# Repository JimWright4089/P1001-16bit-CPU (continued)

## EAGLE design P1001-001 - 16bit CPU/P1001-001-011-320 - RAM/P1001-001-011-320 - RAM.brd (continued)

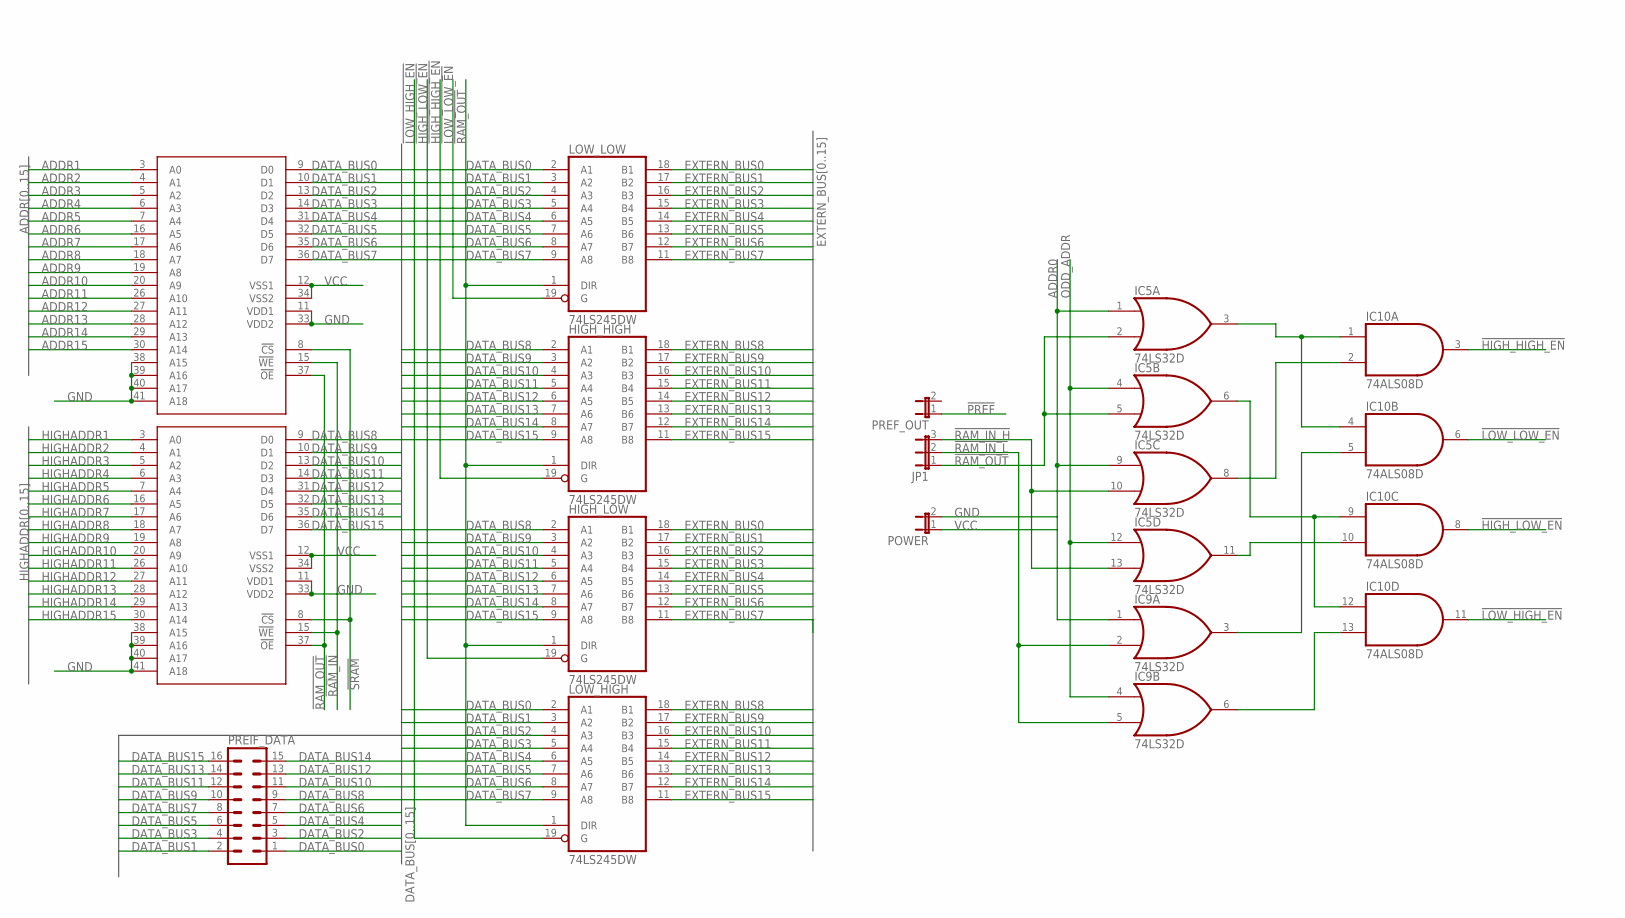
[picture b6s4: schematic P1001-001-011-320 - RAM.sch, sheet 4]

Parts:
HIGH_HIGH: 74LS245DW; SO20W
HIGH_LOW: 74LS245DW; SO20W
IC5, IC9: 74LS32D; SO14
IC10: 74ALS08D; SO14
JP1: JP2E; JP2
LOW_HIGH: 74LS245DW; SO20W
LOW_LOW: 74LS245DW; SO20W
MEM_HIGH: IDT71V424S; TSOP44-II
MEM_LOW: IDT71V424S; TSOP44-II
POWER: JP1E; JP1
PREF_OUT: JP1E; JP1
PREIF_DATA: ML16

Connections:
!HIGH_HIGH_EN: HIGH_HIGH.19 (G), IC10.3 (O)
!HIGH_LOW_EN: HIGH_LOW.19 (G), IC10.8 (O)
!LOW_HIGH_EN: IC10.11 (O), LOW_HIGH.19 (G)
!LOW_LOW_EN: IC10.6 (O), LOW_LOW.19 (G)
!PREF: PREF_OUT.1; also elsewhere on the board
!RAM_IN: MEM_HIGH.15 (!WE), MEM_LOW.15 (!WE)
!RAM_IN_H: IC5.10 (I1), IC5.13 (I1), JP1.3
!RAM_IN_L: IC9.2 (I1), IC9.5 (I1), JP1.2
!RAM_OUT: HIGH_HIGH.1 (DIR), HIGH_LOW.1 (DIR), IC5.2 (I1), IC5.5 (I1), JP1.1, LOW_HIGH.1 (DIR), LOW_LOW.1 (DIR), MEM_HIGH.37 (!OE), MEM_LOW.37 (!OE)
!SRAM: MEM_HIGH.8 (!CS), MEM_LOW.8 (!CS); also elsewhere on the board
ADDR0: IC5.1 (I0), IC5.9 (I0), IC9.1 (I0); also elsewhere on the board
ADDR1: MEM_LOW.3 (A0); also elsewhere on the board
ADDR2: MEM_LOW.4 (A1); also elsewhere on the board
ADDR3: MEM_LOW.5 (A2); also elsewhere on the board
ADDR4: MEM_LOW.6 (A3); also elsewhere on the board
ADDR5: MEM_LOW.7 (A4); also elsewhere on the board
ADDR6: MEM_LOW.16 (A5); also elsewhere on the board
ADDR7: MEM_LOW.17 (A6); also elsewhere on the board
ADDR8: MEM_LOW.18 (A7); also elsewhere on the board
ADDR9: MEM_LOW.19 (A8); also elsewhere on the board
ADDR10: MEM_LOW.20 (A9); also elsewhere on the board
ADDR11: MEM_LOW.26 (A10); also elsewhere on the board
ADDR12: MEM_LOW.27 (A11); also elsewhere on the board
ADDR13: MEM_LOW.28 (A12); also elsewhere on the board
ADDR14: MEM_LOW.29 (A13); also elsewhere on the board
ADDR15: MEM_LOW.30 (A14); also elsewhere on the board
DATA_BUS0: LOW_HIGH.2 (A1), LOW_LOW.2 (A1), MEM_LOW.9 (D0), PREIF_DATA.1; also elsewhere on the board
DATA_BUS1: LOW_HIGH.3 (A2), LOW_LOW.3 (A2), MEM_LOW.10 (D1), PREIF_DATA.2; also elsewhere on the board
DATA_BUS2: LOW_HIGH.4 (A3), LOW_LOW.4 (A3), MEM_LOW.13 (D2), PREIF_DATA.3; also elsewhere on the board
DATA_BUS3: LOW_HIGH.5 (A4), LOW_LOW.5 (A4), MEM_LOW.14 (D3), PREIF_DATA.4; also elsewhere on the board
DATA_BUS4: LOW_HIGH.6 (A5), LOW_LOW.6 (A5), MEM_LOW.31 (D4), PREIF_DATA.5; also elsewhere on the board
DATA_BUS5: LOW_HIGH.7 (A6), LOW_LOW.7 (A6), MEM_LOW.32 (D5), PREIF_DATA.6; also elsewhere on the board
DATA_BUS6: LOW_HIGH.8 (A7), LOW_LOW.8 (A7), MEM_LOW.35 (D6), PREIF_DATA.7; also elsewhere on the board
DATA_BUS7: LOW_HIGH.9 (A8), LOW_LOW.9 (A8), MEM_LOW.36 (D7), PREIF_DATA.8; also elsewhere on the board
DATA_BUS8: HIGH_HIGH.2 (A1), HIGH_LOW.2 (A1), MEM_HIGH.9 (D0), PREIF_DATA.9; also elsewhere on the board
DATA_BUS9: HIGH_HIGH.3 (A2), HIGH_LOW.3 (A2), MEM_HIGH.10 (D1), PREIF_DATA.10; also elsewhere on the board
DATA_BUS10: HIGH_HIGH.4 (A3), HIGH_LOW.4 (A3), MEM_HIGH.13 (D2), PREIF_DATA.11; also elsewhere on the board
DATA_BUS11: HIGH_HIGH.5 (A4), HIGH_LOW.5 (A4), MEM_HIGH.14 (D3), PREIF_DATA.12; also elsewhere on the board
DATA_BUS12: HIGH_HIGH.6 (A5), HIGH_LOW.6 (A5), MEM_HIGH.31 (D4), PREIF_DATA.13; also elsewhere on the board
DATA_BUS13: HIGH_HIGH.7 (A6), HIGH_LOW.7 (A6), MEM_HIGH.32 (D5), PREIF_DATA.14; also elsewhere on the board
DATA_BUS14: HIGH_HIGH.8 (A7), HIGH_LOW.8 (A7), MEM_HIGH.35 (D6), PREIF_DATA.15; also elsewhere on the board
DATA_BUS15: HIGH_HIGH.9 (A8), HIGH_LOW.9 (A8), MEM_HIGH.36 (D7), PREIF_DATA.16; also elsewhere on the board
EXTERN_BUS0: HIGH_LOW.18 (B1), LOW_LOW.18 (B1); also elsewhere on the board
EXTERN_BUS1: HIGH_LOW.17 (B2), LOW_LOW.17 (B2); also elsewhere on the board
EXTERN_BUS2: HIGH_LOW.16 (B3), LOW_LOW.16 (B3); also elsewhere on the board
EXTERN_BUS3: HIGH_LOW.15 (B4), LOW_LOW.15 (B4); also elsewhere on the board
EXTERN_BUS4: HIGH_LOW.14 (B5), LOW_LOW.14 (B5); also elsewhere on the board
EXTERN_BUS5: HIGH_LOW.13 (B6), LOW_LOW.13 (B6); also elsewhere on the board
EXTERN_BUS6: HIGH_LOW.12 (B7), LOW_LOW.12 (B7); also elsewhere on the board
EXTERN_BUS7: HIGH_LOW.11 (B8), LOW_LOW.11 (B8); also elsewhere on the board
EXTERN_BUS8: HIGH_HIGH.18 (B1), LOW_HIGH.18 (B1); also elsewhere on the board
EXTERN_BUS9: HIGH_HIGH.17 (B2), LOW_HIGH.17 (B2); also elsewhere on the board
EXTERN_BUS10: HIGH_HIGH.16 (B3), LOW_HIGH.16 (B3); also elsewhere on the board
EXTERN_BUS11: HIGH_HIGH.15 (B4), LOW_HIGH.15 (B4); also elsewhere on the board
EXTERN_BUS12: HIGH_HIGH.14 (B5), LOW_HIGH.14 (B5); also elsewhere on the board
EXTERN_BUS13: HIGH_HIGH.13 (B6), LOW_HIGH.13 (B6); also elsewhere on the board
EXTERN_BUS14: HIGH_HIGH.12 (B7), LOW_HIGH.12 (B7); also elsewhere on the board
EXTERN_BUS15: HIGH_HIGH.11 (B8), LOW_HIGH.11 (B8); also elsewhere on the board
GND: HIGH_HIGH.10 (GND), HIGH_LOW.10 (GND), IC5.7 (GND), IC9.7 (GND), IC10.7 (GND), LOW_HIGH.10 (GND), LOW_LOW.10 (GND), MEM_HIGH.11 (VDD1), MEM_HIGH.33 (VDD2), MEM_HIGH.38 (A15), MEM_HIGH.39 (A16), MEM_HIGH.40 (A17), MEM_HIGH.41 (A18), MEM_LOW.11 (VDD1), MEM_LOW.33 (VDD2), MEM_LOW.38 (A15), MEM_LOW.39 (A16), MEM_LOW.40 (A17), MEM_LOW.41 (A18), POWER.2; also elsewhere on the board
HIGHADDR1: MEM_HIGH.3 (A0); also elsewhere on the board
HIGHADDR2: MEM_HIGH.4 (A1); also elsewhere on the board
HIGHADDR3: MEM_HIGH.5 (A2); also elsewhere on the board
HIGHADDR4: MEM_HIGH.6 (A3); also elsewhere on the board
HIGHADDR5: MEM_HIGH.7 (A4); also elsewhere on the board
HIGHADDR6: MEM_HIGH.16 (A5); also elsewhere on the board
HIGHADDR7: MEM_HIGH.17 (A6); also elsewhere on the board
HIGHADDR8: MEM_HIGH.18 (A7); also elsewhere on the board
HIGHADDR9: MEM_HIGH.19 (A8); also elsewhere on the board
HIGHADDR10: MEM_HIGH.20 (A9); also elsewhere on the board
HIGHADDR11: MEM_HIGH.26 (A10); also elsewhere on the board
HIGHADDR12: MEM_HIGH.27 (A11); also elsewhere on the board
HIGHADDR13: MEM_HIGH.28 (A12); also elsewhere on the board
HIGHADDR14: MEM_HIGH.29 (A13); also elsewhere on the board
HIGHADDR15: MEM_HIGH.30 (A14); also elsewhere on the board
unnamed: IC5.3 (O), IC10.1 (I0), IC10.4 (I0)
unnamed: IC5.8 (O), IC10.2 (I1)
unnamed: IC9.3 (O), IC10.5 (I1)
unnamed: IC5.6 (O), IC10.9 (I0), IC10.12 (I0)
unnamed: IC5.11 (O), IC10.10 (I1)
unnamed: IC9.6 (O), IC10.13 (I1)
ODD_ADDR: IC5.4 (I0), IC5.12 (I0), IC9.4 (I0); also elsewhere on the board
VCC: HIGH_HIGH.20 (VCC), HIGH_LOW.20 (VCC), IC5.14 (VCC), IC9.14 (VCC), IC10.14 (VCC), LOW_HIGH.20 (VCC), LOW_LOW.20 (VCC), MEM_HIGH.12 (VSS1), MEM_HIGH.34 (VSS2), MEM_LOW.12 (VSS1), MEM_LOW.34 (VSS2), POWER.1; also elsewhere on the board

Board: 2 copper layers, 46 parts (4 on the bottom side), 118 nets, no tracks yet.

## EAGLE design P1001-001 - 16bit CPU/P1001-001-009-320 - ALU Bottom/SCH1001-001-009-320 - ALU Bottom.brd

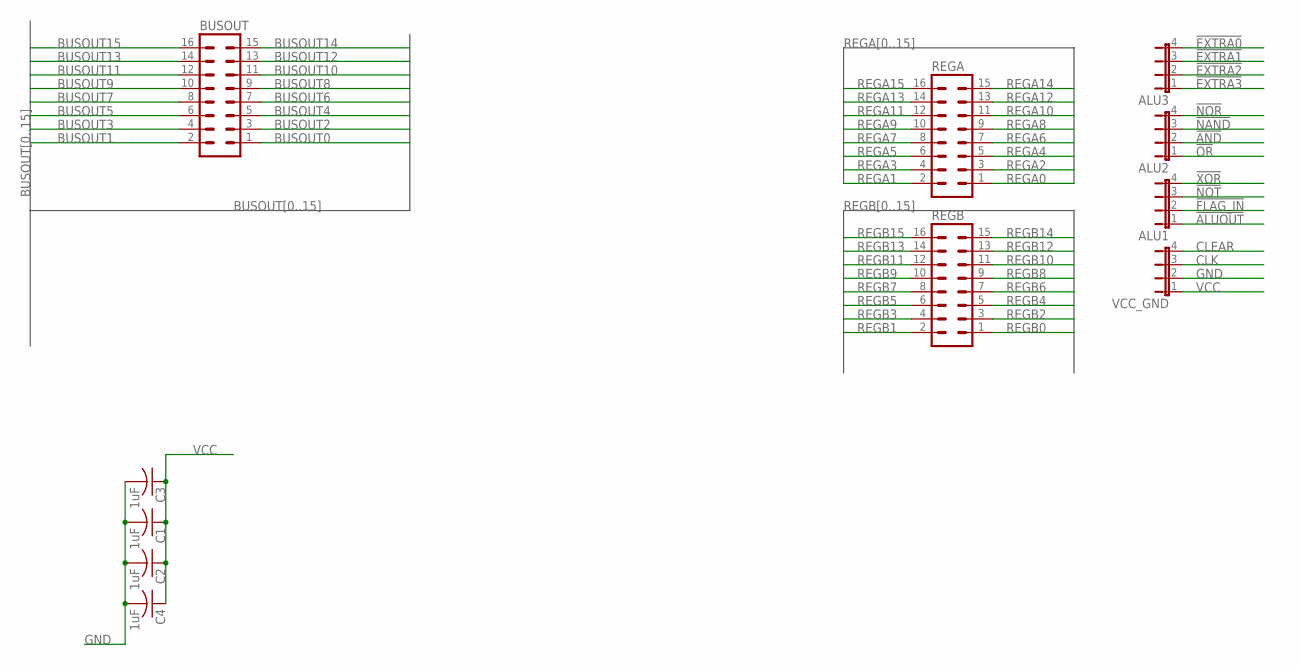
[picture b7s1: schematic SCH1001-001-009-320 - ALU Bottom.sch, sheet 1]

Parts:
ALU1, ALU2, ALU3: JP4E; JP4
BUSOUT: ML16
C1, C2, C3, C4: 1uF; C1206
REGA: ML16
REGB: ML16
VCC_GND: JP4E; JP4

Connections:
!ALUOUT: ALU1.1
!AND: ALU2.2; also elsewhere on the board
!EXTRA0: ALU3.4
!EXTRA1: ALU3.3
!EXTRA2: ALU3.2
!EXTRA3: ALU3.1
!FLAG_IN: ALU1.2
!NAND: ALU2.3; also elsewhere on the board
!NOR: ALU2.4; also elsewhere on the board
!NOT: ALU1.3; also elsewhere on the board
!OR: ALU2.1; also elsewhere on the board
!XOR: ALU1.4; also elsewhere on the board
BUSOUT0: BUSOUT.1; also elsewhere on the board
BUSOUT1: BUSOUT.2; also elsewhere on the board
BUSOUT2: BUSOUT.3; also elsewhere on the board
BUSOUT3: BUSOUT.4; also elsewhere on the board
BUSOUT4: BUSOUT.5; also elsewhere on the board
BUSOUT5: BUSOUT.6; also elsewhere on the board
BUSOUT6: BUSOUT.7; also elsewhere on the board
BUSOUT7: BUSOUT.8; also elsewhere on the board
BUSOUT8: BUSOUT.9; also elsewhere on the board
BUSOUT9: BUSOUT.10; also elsewhere on the board
BUSOUT10: BUSOUT.11; also elsewhere on the board
BUSOUT11: BUSOUT.12; also elsewhere on the board
BUSOUT12: BUSOUT.13; also elsewhere on the board
BUSOUT13: BUSOUT.14; also elsewhere on the board
BUSOUT14: BUSOUT.15; also elsewhere on the board
BUSOUT15: BUSOUT.16; also elsewhere on the board
CLEAR: VCC_GND.4
CLK: VCC_GND.3
GND: C1.2, C2.2, C3.2, C4.2, VCC_GND.2; also elsewhere on the board
REGA0: REGA.1; also elsewhere on the board
REGA1: REGA.2; also elsewhere on the board
REGA2: REGA.3; also elsewhere on the board
REGA3: REGA.4; also elsewhere on the board
REGA4: REGA.5; also elsewhere on the board
REGA5: REGA.6; also elsewhere on the board
REGA6: REGA.7; also elsewhere on the board
REGA7: REGA.8; also elsewhere on the board
REGA8: REGA.9; also elsewhere on the board
REGA9: REGA.10; also elsewhere on the board
REGA10: REGA.11; also elsewhere on the board
REGA11: REGA.12; also elsewhere on the board
REGA12: REGA.13; also elsewhere on the board
REGA13: REGA.14; also elsewhere on the board
REGA14: REGA.15; also elsewhere on the board
REGA15: REGA.16; also elsewhere on the board
REGB0: REGB.1; also elsewhere on the board
REGB1: REGB.2; also elsewhere on the board
REGB2: REGB.3; also elsewhere on the board
REGB3: REGB.4; also elsewhere on the board
REGB4: REGB.5; also elsewhere on the board
REGB5: REGB.6; also elsewhere on the board
REGB6: REGB.7; also elsewhere on the board
REGB7: REGB.8; also elsewhere on the board
REGB8: REGB.9; also elsewhere on the board
REGB9: REGB.10; also elsewhere on the board
REGB10: REGB.11; also elsewhere on the board
REGB11: REGB.12; also elsewhere on the board
REGB12: REGB.13; also elsewhere on the board
REGB13: REGB.14; also elsewhere on the board
REGB14: REGB.15; also elsewhere on the board
REGB15: REGB.16; also elsewhere on the board
VCC: C1.1, C2.1, C3.1, C4.1, VCC_GND.1; also elsewhere on the board

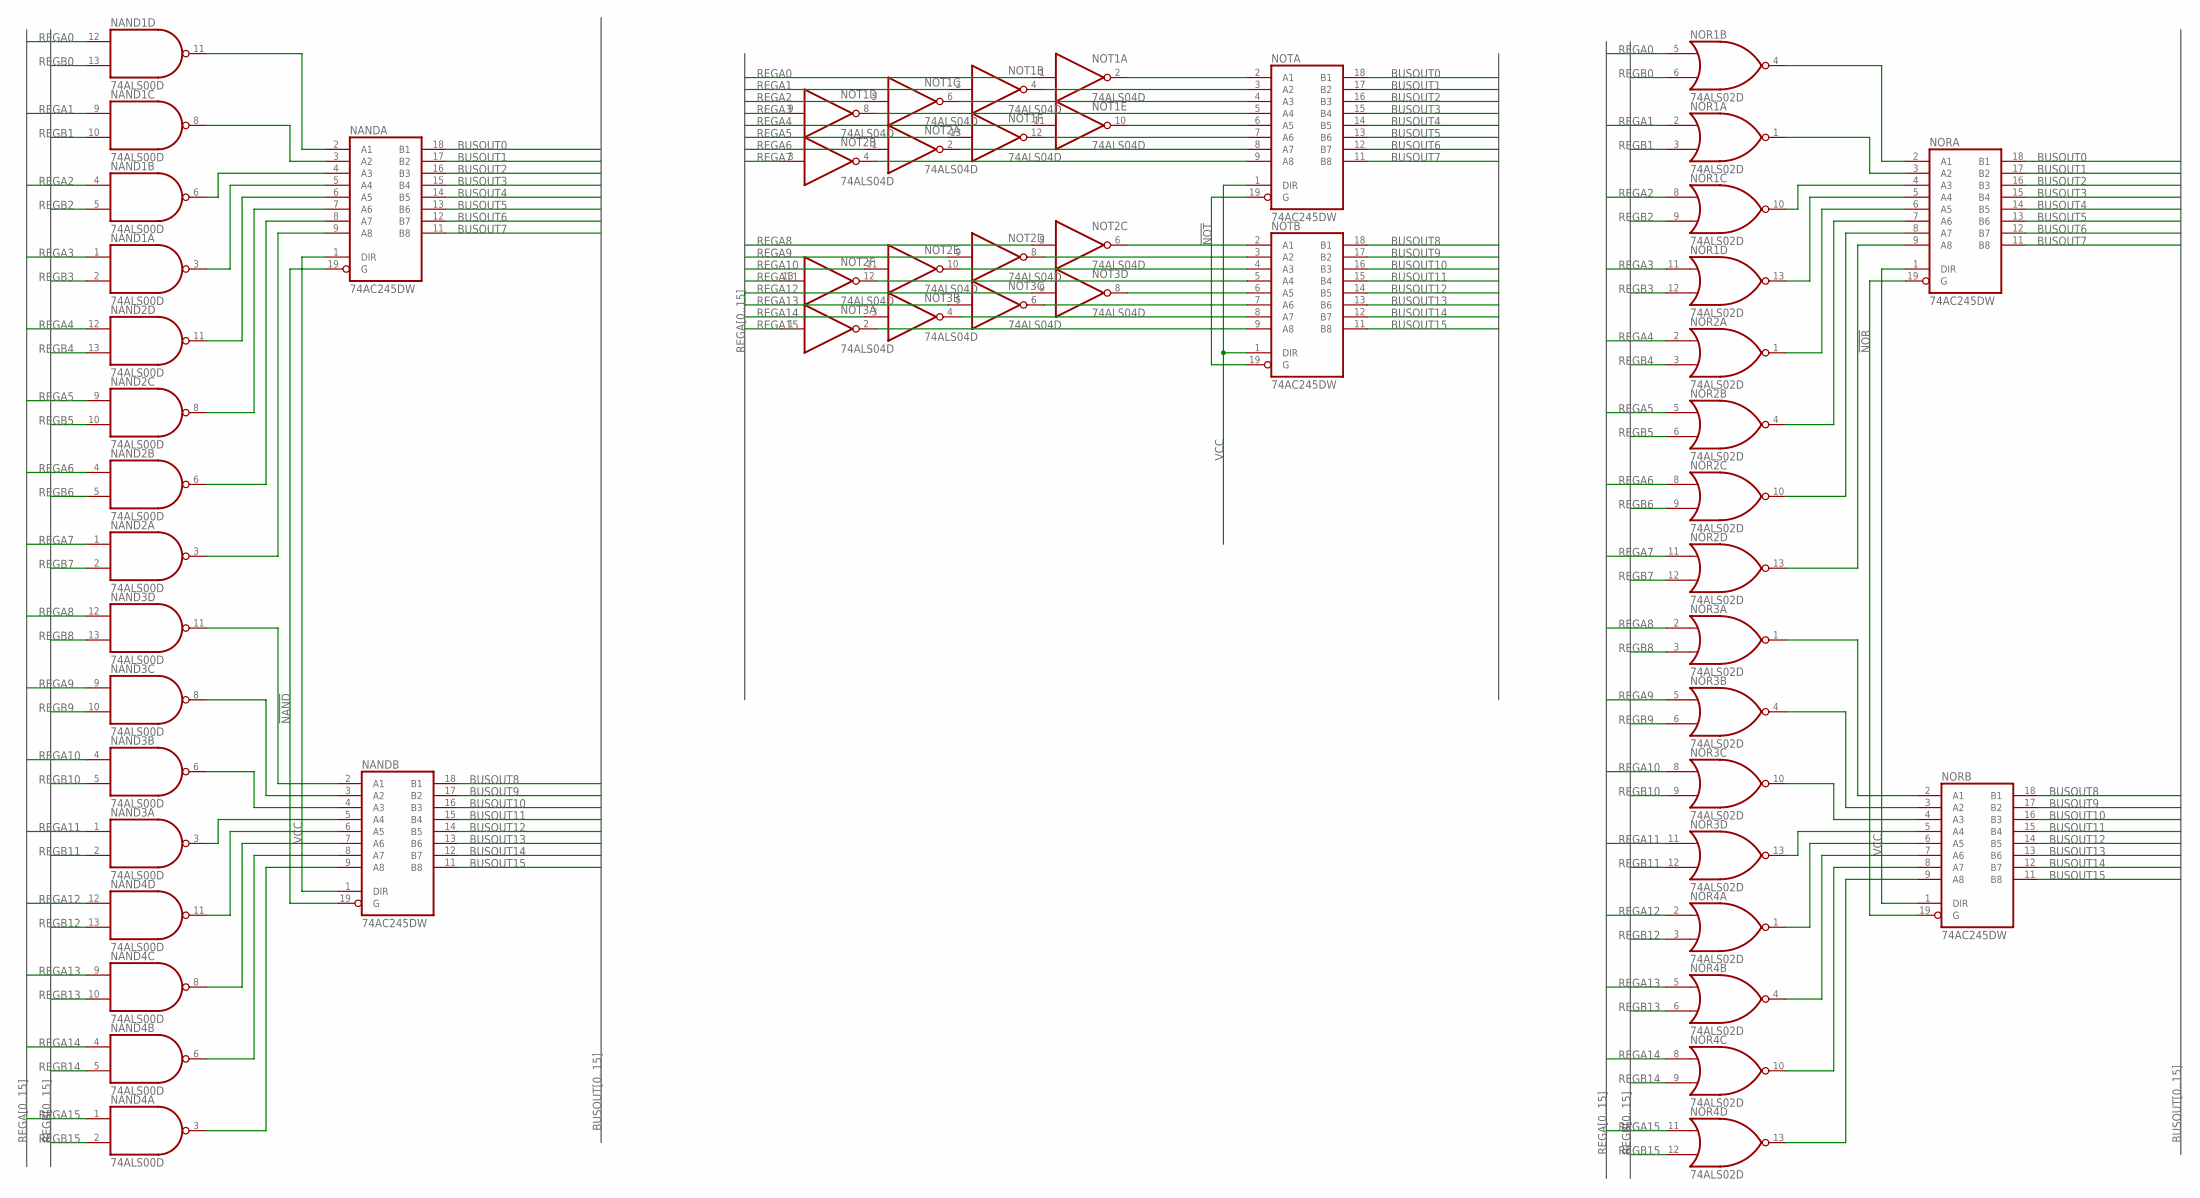
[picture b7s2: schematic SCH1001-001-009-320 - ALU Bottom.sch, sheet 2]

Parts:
NAND1, NAND2, NAND3, NAND4: 74ALS00D; SO14
NANDA: 74AC245DW; SO20W
NANDB: 74AC245DW; SO20W
NOR1, NOR2, NOR3, NOR4: 74ALS02D; SO14
NORA: 74AC245DW; SO20W
NORB: 74AC245DW; SO20W
NOT1, NOT2, NOT3: 74ALS04D; SO14
NOTA: 74AC245DW; SO20W
NOTB: 74AC245DW; SO20W

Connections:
!NAND: NANDA.19 (G), NANDB.19 (G); also elsewhere on the board
!NOR: NORA.19 (G), NORB.19 (G); also elsewhere on the board
!NOT: NOTA.19 (G), NOTB.19 (G); also elsewhere on the board
BUSOUT0: NANDA.18 (B1), NORA.18 (B1), NOTA.18 (B1); also elsewhere on the board
BUSOUT1: NANDA.17 (B2), NORA.17 (B2), NOTA.17 (B2); also elsewhere on the board
BUSOUT2: NANDA.16 (B3), NORA.16 (B3), NOTA.16 (B3); also elsewhere on the board
BUSOUT3: NANDA.15 (B4), NORA.15 (B4), NOTA.15 (B4); also elsewhere on the board
BUSOUT4: NANDA.14 (B5), NORA.14 (B5), NOTA.14 (B5); also elsewhere on the board
BUSOUT5: NANDA.13 (B6), NORA.13 (B6), NOTA.13 (B6); also elsewhere on the board
BUSOUT6: NANDA.12 (B7), NORA.12 (B7), NOTA.12 (B7); also elsewhere on the board
BUSOUT7: NANDA.11 (B8), NORA.11 (B8), NOTA.11 (B8); also elsewhere on the board
BUSOUT8: NANDB.18 (B1), NORB.18 (B1), NOTB.18 (B1); also elsewhere on the board
BUSOUT9: NANDB.17 (B2), NORB.17 (B2), NOTB.17 (B2); also elsewhere on the board
BUSOUT10: NANDB.16 (B3), NORB.16 (B3), NOTB.16 (B3); also elsewhere on the board
BUSOUT11: NANDB.15 (B4), NORB.15 (B4), NOTB.15 (B4); also elsewhere on the board
BUSOUT12: NANDB.14 (B5), NORB.14 (B5), NOTB.14 (B5); also elsewhere on the board
BUSOUT13: NANDB.13 (B6), NORB.13 (B6), NOTB.13 (B6); also elsewhere on the board
BUSOUT14: NANDB.12 (B7), NORB.12 (B7), NOTB.12 (B7); also elsewhere on the board
BUSOUT15: NANDB.11 (B8), NORB.11 (B8), NOTB.11 (B8); also elsewhere on the board
GND: NAND1.7 (GND), NAND2.7 (GND), NAND3.7 (GND), NAND4.7 (GND), NANDA.10 (GND), NANDB.10 (GND), NOR1.7 (GND), NOR2.7 (GND), NOR3.7 (GND), NOR4.7 (GND), NORA.10 (GND), NORB.10 (GND), NOT1.7 (GND), NOT2.7 (GND), NOT3.7 (GND), NOTA.10 (GND), NOTB.10 (GND); also elsewhere on the board
unnamed: NOT1.2 (O), NOTA.2 (A1)
unnamed: NOT1.10 (O), NOTA.6 (A5)
unnamed: NOT1.4 (O), NOTA.3 (A2)
unnamed: NOT1.12 (O), NOTA.7 (A6)
unnamed: NOT2.2 (O), NOTA.8 (A7)
unnamed: NOT1.6 (O), NOTA.4 (A3)
unnamed: NOT1.8 (O), NOTA.5 (A4)
unnamed: NOT2.4 (O), NOTA.9 (A8)
unnamed: NOT2.6 (O), NOTB.2 (A1)
unnamed: NOT3.8 (O), NOTB.6 (A5)
unnamed: NOT2.8 (O), NOTB.3 (A2)
unnamed: NOT3.6 (O), NOTB.7 (A6)
unnamed: NOT3.4 (O), NOTB.8 (A7)
unnamed: NOT2.10 (O), NOTB.4 (A3)
unnamed: NOT2.12 (O), NOTB.5 (A4)
unnamed: NOT3.2 (O), NOTB.9 (A8)
unnamed: NAND1.11 (O), NANDA.2 (A1)
unnamed: NAND1.8 (O), NANDA.3 (A2)
unnamed: NAND1.6 (O), NANDA.4 (A3)
unnamed: NAND1.3 (O), NANDA.5 (A4)
unnamed: NAND2.11 (O), NANDA.6 (A5)
unnamed: NAND2.8 (O), NANDA.7 (A6)
unnamed: NAND2.6 (O), NANDA.8 (A7)
unnamed: NAND2.3 (O), NANDA.9 (A8)
unnamed: NAND3.11 (O), NANDB.2 (A1)
unnamed: NAND3.8 (O), NANDB.3 (A2)
unnamed: NAND3.6 (O), NANDB.4 (A3)
unnamed: NAND3.3 (O), NANDB.5 (A4)
unnamed: NAND4.11 (O), NANDB.6 (A5)
unnamed: NAND4.8 (O), NANDB.7 (A6)
unnamed: NAND4.6 (O), NANDB.8 (A7)
unnamed: NAND4.3 (O), NANDB.9 (A8)
unnamed: NOR1.4 (O), NORA.2 (A1)
unnamed: NOR1.1 (O), NORA.3 (A2)
unnamed: NOR1.10 (O), NORA.4 (A3)
unnamed: NOR1.13 (O), NORA.5 (A4)
unnamed: NOR2.1 (O), NORA.6 (A5)
unnamed: NOR2.4 (O), NORA.7 (A6)
unnamed: NOR2.10 (O), NORA.8 (A7)
unnamed: NOR2.13 (O), NORA.9 (A8)
unnamed: NOR3.1 (O), NORB.2 (A1)
unnamed: NOR3.4 (O), NORB.3 (A2)
unnamed: NOR3.10 (O), NORB.4 (A3)
unnamed: NOR3.13 (O), NORB.5 (A4)
unnamed: NOR4.1 (O), NORB.6 (A5)
unnamed: NOR4.4 (O), NORB.7 (A6)
unnamed: NOR4.10 (O), NORB.8 (A7)
unnamed: NOR4.13 (O), NORB.9 (A8)
REGA0: NAND1.12 (I0), NOR1.5 (I0), NOT1.1 (I); also elsewhere on the board
REGA1: NAND1.9 (I0), NOR1.2 (I0), NOT1.3 (I); also elsewhere on the board
REGA2: NAND1.4 (I0), NOR1.8 (I0), NOT1.5 (I); also elsewhere on the board
REGA3: NAND1.1 (I0), NOR1.11 (I0), NOT1.9 (I); also elsewhere on the board
REGA4: NAND2.12 (I0), NOR2.2 (I0), NOT1.11 (I); also elsewhere on the board
REGA5: NAND2.9 (I0), NOR2.5 (I0), NOT1.13 (I); also elsewhere on the board
REGA6: NAND2.4 (I0), NOR2.8 (I0), NOT2.1 (I); also elsewhere on the board
REGA7: NAND2.1 (I0), NOR2.11 (I0), NOT2.3 (I); also elsewhere on the board
REGA8: NAND3.12 (I0), NOR3.2 (I0), NOT2.5 (I); also elsewhere on the board
REGA9: NAND3.9 (I0), NOR3.5 (I0), NOT2.9 (I); also elsewhere on the board
REGA10: NAND3.4 (I0), NOR3.8 (I0), NOT2.11 (I); also elsewhere on the board
REGA11: NAND3.1 (I0), NOR3.11 (I0), NOT2.13 (I); also elsewhere on the board
REGA12: NAND4.12 (I0), NOR4.2 (I0), NOT3.9 (I); also elsewhere on the board
REGA13: NAND4.9 (I0), NOR4.5 (I0), NOT3.5 (I); also elsewhere on the board
REGA14: NAND4.4 (I0), NOR4.8 (I0), NOT3.3 (I); also elsewhere on the board
REGA15: NAND4.1 (I0), NOR4.11 (I0), NOT3.1 (I); also elsewhere on the board
REGB0: NAND1.13 (I1), NOR1.6 (I1); also elsewhere on the board
REGB1: NAND1.10 (I1), NOR1.3 (I1); also elsewhere on the board
REGB2: NAND1.5 (I1), NOR1.9 (I1); also elsewhere on the board
REGB3: NAND1.2 (I1), NOR1.12 (I1); also elsewhere on the board
REGB4: NAND2.13 (I1), NOR2.3 (I1); also elsewhere on the board
REGB5: NAND2.10 (I1), NOR2.6 (I1); also elsewhere on the board
REGB6: NAND2.5 (I1), NOR2.9 (I1); also elsewhere on the board
REGB7: NAND2.2 (I1), NOR2.12 (I1); also elsewhere on the board
REGB8: NAND3.13 (I1), NOR3.3 (I1); also elsewhere on the board
REGB9: NAND3.10 (I1), NOR3.6 (I1); also elsewhere on the board
REGB10: NAND3.5 (I1), NOR3.9 (I1); also elsewhere on the board
REGB11: NAND3.2 (I1), NOR3.12 (I1); also elsewhere on the board
REGB12: NAND4.13 (I1), NOR4.3 (I1); also elsewhere on the board
REGB13: NAND4.10 (I1), NOR4.6 (I1); also elsewhere on the board
REGB14: NAND4.5 (I1), NOR4.9 (I1); also elsewhere on the board
REGB15: NAND4.2 (I1), NOR4.12 (I1); also elsewhere on the board
VCC: NAND1.14 (VCC), NAND2.14 (VCC), NAND3.14 (VCC), NAND4.14 (VCC), NANDA.1 (DIR), NANDA.20 (VCC), NANDB.1 (DIR), NANDB.20 (VCC), NOR1.14 (VCC), NOR2.14 (VCC), NOR3.14 (VCC), NOR4.14 (VCC), NORA.1 (DIR), NORA.20 (VCC), NORB.1 (DIR), NORB.20 (VCC), NOT1.14 (VCC), NOT2.14 (VCC), NOT3.14 (VCC), NOTA.1 (DIR), NOTA.20 (VCC), NOTB.1 (DIR), NOTB.20 (VCC); also elsewhere on the board

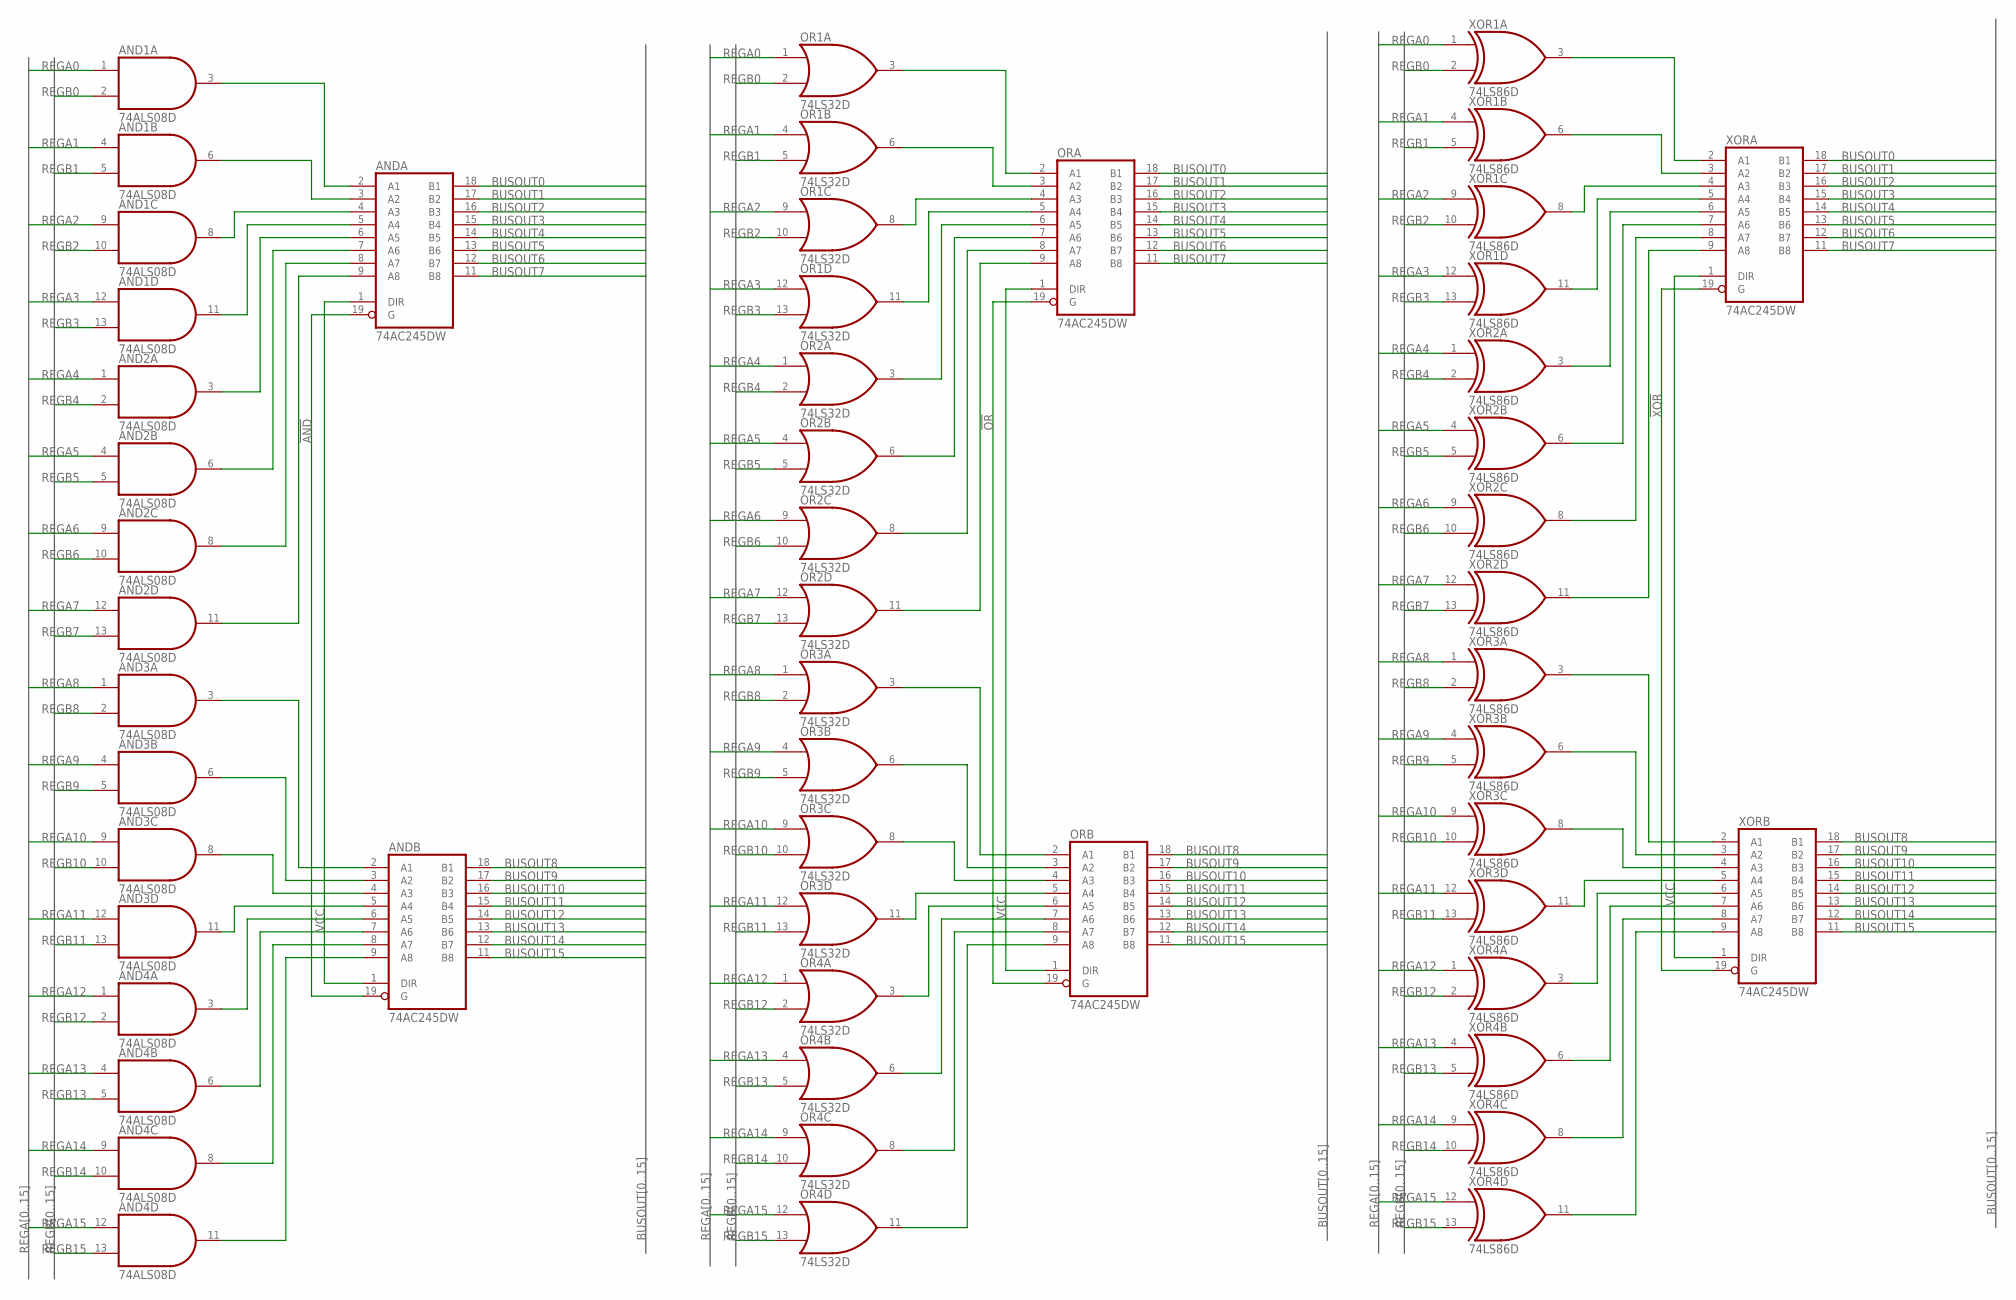
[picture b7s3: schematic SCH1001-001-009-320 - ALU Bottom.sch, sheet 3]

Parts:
AND1, AND2, AND3, AND4: 74ALS08D; SO14
ANDA: 74AC245DW; SO20W
ANDB: 74AC245DW; SO20W
OR1, OR2, OR3, OR4: 74LS32D; SO14
ORA: 74AC245DW; SO20W
ORB: 74AC245DW; SO20W
XOR1, XOR2, XOR3, XOR4: 74LS86D; SO14
XORA: 74AC245DW; SO20W
XORB: 74AC245DW; SO20W

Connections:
!AND: ANDA.19 (G), ANDB.19 (G); also elsewhere on the board
!OR: ORA.19 (G), ORB.19 (G); also elsewhere on the board
!XOR: XORA.19 (G), XORB.19 (G); also elsewhere on the board
BUSOUT0: ANDA.18 (B1), ORA.18 (B1), XORA.18 (B1); also elsewhere on the board
BUSOUT1: ANDA.17 (B2), ORA.17 (B2), XORA.17 (B2); also elsewhere on the board
BUSOUT2: ANDA.16 (B3), ORA.16 (B3), XORA.16 (B3); also elsewhere on the board
BUSOUT3: ANDA.15 (B4), ORA.15 (B4), XORA.15 (B4); also elsewhere on the board
BUSOUT4: ANDA.14 (B5), ORA.14 (B5), XORA.14 (B5); also elsewhere on the board
BUSOUT5: ANDA.13 (B6), ORA.13 (B6), XORA.13 (B6); also elsewhere on the board
BUSOUT6: ANDA.12 (B7), ORA.12 (B7), XORA.12 (B7); also elsewhere on the board
BUSOUT7: ANDA.11 (B8), ORA.11 (B8), XORA.11 (B8); also elsewhere on the board
BUSOUT8: ANDB.18 (B1), ORB.18 (B1), XORB.18 (B1); also elsewhere on the board
BUSOUT9: ANDB.17 (B2), ORB.17 (B2), XORB.17 (B2); also elsewhere on the board
BUSOUT10: ANDB.16 (B3), ORB.16 (B3), XORB.16 (B3); also elsewhere on the board
BUSOUT11: ANDB.15 (B4), ORB.15 (B4), XORB.15 (B4); also elsewhere on the board
BUSOUT12: ANDB.14 (B5), ORB.14 (B5), XORB.14 (B5); also elsewhere on the board
BUSOUT13: ANDB.13 (B6), ORB.13 (B6), XORB.13 (B6); also elsewhere on the board
BUSOUT14: ANDB.12 (B7), ORB.12 (B7), XORB.12 (B7); also elsewhere on the board
BUSOUT15: ANDB.11 (B8), ORB.11 (B8), XORB.11 (B8); also elsewhere on the board
GND: AND1.7 (GND), AND2.7 (GND), AND3.7 (GND), AND4.7 (GND), ANDA.10 (GND), ANDB.10 (GND), OR1.7 (GND), OR2.7 (GND), OR3.7 (GND), OR4.7 (GND), ORA.10 (GND), ORB.10 (GND), XOR1.7 (GND), XOR2.7 (GND), XOR3.7 (GND), XOR4.7 (GND), XORA.10 (GND), XORB.10 (GND); also elsewhere on the board
unnamed: AND1.3 (O), ANDA.2 (A1)
unnamed: AND1.6 (O), ANDA.3 (A2)
unnamed: AND1.8 (O), ANDA.4 (A3)
unnamed: AND1.11 (O), ANDA.5 (A4)
unnamed: AND2.3 (O), ANDA.6 (A5)
unnamed: AND2.6 (O), ANDA.7 (A6)
unnamed: AND2.8 (O), ANDA.8 (A7)
unnamed: AND2.11 (O), ANDA.9 (A8)
unnamed: AND3.3 (O), ANDB.2 (A1)
unnamed: AND3.6 (O), ANDB.3 (A2)
unnamed: AND3.8 (O), ANDB.4 (A3)
unnamed: AND3.11 (O), ANDB.5 (A4)
unnamed: AND4.3 (O), ANDB.6 (A5)
unnamed: AND4.6 (O), ANDB.7 (A6)
unnamed: AND4.8 (O), ANDB.8 (A7)
unnamed: AND4.11 (O), ANDB.9 (A8)
unnamed: OR1.3 (O), ORA.2 (A1)
unnamed: OR1.6 (O), ORA.3 (A2)
unnamed: OR1.8 (O), ORA.4 (A3)
unnamed: OR1.11 (O), ORA.5 (A4)
unnamed: OR2.3 (O), ORA.6 (A5)
unnamed: OR2.6 (O), ORA.7 (A6)
unnamed: OR2.8 (O), ORA.8 (A7)
unnamed: OR2.11 (O), ORA.9 (A8)
unnamed: OR3.3 (O), ORB.2 (A1)
unnamed: OR3.6 (O), ORB.3 (A2)
unnamed: OR3.8 (O), ORB.4 (A3)
unnamed: OR3.11 (O), ORB.5 (A4)
unnamed: OR4.3 (O), ORB.6 (A5)
unnamed: OR4.6 (O), ORB.7 (A6)
unnamed: OR4.8 (O), ORB.8 (A7)
unnamed: OR4.11 (O), ORB.9 (A8)
unnamed: XOR1.3 (O), XORA.2 (A1)
unnamed: XOR1.6 (O), XORA.3 (A2)
unnamed: XOR1.8 (O), XORA.4 (A3)
unnamed: XOR1.11 (O), XORA.5 (A4)
unnamed: XOR2.3 (O), XORA.6 (A5)
unnamed: XOR2.6 (O), XORA.7 (A6)
unnamed: XOR2.8 (O), XORA.8 (A7)
unnamed: XOR2.11 (O), XORA.9 (A8)
unnamed: XOR3.3 (O), XORB.2 (A1)
unnamed: XOR3.6 (O), XORB.3 (A2)
unnamed: XOR3.8 (O), XORB.4 (A3)
unnamed: XOR3.11 (O), XORB.5 (A4)
unnamed: XOR4.3 (O), XORB.6 (A5)
unnamed: XOR4.6 (O), XORB.7 (A6)
unnamed: XOR4.8 (O), XORB.8 (A7)
unnamed: XOR4.11 (O), XORB.9 (A8)
REGA0: AND1.1 (I0), OR1.1 (I0), XOR1.1 (I0); also elsewhere on the board
REGA1: AND1.4 (I0), OR1.4 (I0), XOR1.4 (I0); also elsewhere on the board
REGA2: AND1.9 (I0), OR1.9 (I0), XOR1.9 (I0); also elsewhere on the board
REGA3: AND1.12 (I0), OR1.12 (I0), XOR1.12 (I0); also elsewhere on the board
REGA4: AND2.1 (I0), OR2.1 (I0), XOR2.1 (I0); also elsewhere on the board
REGA5: AND2.4 (I0), OR2.4 (I0), XOR2.4 (I0); also elsewhere on the board
REGA6: AND2.9 (I0), OR2.9 (I0), XOR2.9 (I0); also elsewhere on the board
REGA7: AND2.12 (I0), OR2.12 (I0), XOR2.12 (I0); also elsewhere on the board
REGA8: AND3.1 (I0), OR3.1 (I0), XOR3.1 (I0); also elsewhere on the board
REGA9: AND3.4 (I0), OR3.4 (I0), XOR3.4 (I0); also elsewhere on the board
REGA10: AND3.9 (I0), OR3.9 (I0), XOR3.9 (I0); also elsewhere on the board
REGA11: AND3.12 (I0), OR3.12 (I0), XOR3.12 (I0); also elsewhere on the board
REGA12: AND4.1 (I0), OR4.1 (I0), XOR4.1 (I0); also elsewhere on the board
REGA13: AND4.4 (I0), OR4.4 (I0), XOR4.4 (I0); also elsewhere on the board
REGA14: AND4.9 (I0), OR4.9 (I0), XOR4.9 (I0); also elsewhere on the board
REGA15: AND4.12 (I0), OR4.12 (I0), XOR4.12 (I0); also elsewhere on the board
REGB0: AND1.2 (I1), OR1.2 (I1), XOR1.2 (I1); also elsewhere on the board
REGB1: AND1.5 (I1), OR1.5 (I1), XOR1.5 (I1); also elsewhere on the board
REGB2: AND1.10 (I1), OR1.10 (I1), XOR1.10 (I1); also elsewhere on the board
REGB3: AND1.13 (I1), OR1.13 (I1), XOR1.13 (I1); also elsewhere on the board
REGB4: AND2.2 (I1), OR2.2 (I1), XOR2.2 (I1); also elsewhere on the board
REGB5: AND2.5 (I1), OR2.5 (I1), XOR2.5 (I1); also elsewhere on the board
REGB6: AND2.10 (I1), OR2.10 (I1), XOR2.10 (I1); also elsewhere on the board
REGB7: AND2.13 (I1), OR2.13 (I1), XOR2.13 (I1); also elsewhere on the board
REGB8: AND3.2 (I1), OR3.2 (I1), XOR3.2 (I1); also elsewhere on the board
REGB9: AND3.5 (I1), OR3.5 (I1), XOR3.5 (I1); also elsewhere on the board
REGB10: AND3.10 (I1), OR3.10 (I1), XOR3.10 (I1); also elsewhere on the board
REGB11: AND3.13 (I1), OR3.13 (I1), XOR3.13 (I1); also elsewhere on the board
REGB12: AND4.2 (I1), OR4.2 (I1), XOR4.2 (I1); also elsewhere on the board
REGB13: AND4.5 (I1), OR4.5 (I1), XOR4.5 (I1); also elsewhere on the board
REGB14: AND4.10 (I1), OR4.10 (I1), XOR4.10 (I1); also elsewhere on the board
REGB15: AND4.13 (I1), OR4.13 (I1), XOR4.13 (I1); also elsewhere on the board
VCC: AND1.14 (VCC), AND2.14 (VCC), AND3.14 (VCC), AND4.14 (VCC), ANDA.1 (DIR), ANDA.20 (VCC), ANDB.1 (DIR), ANDB.20 (VCC), OR1.14 (VCC), OR2.14 (VCC), OR3.14 (VCC), OR4.14 (VCC), ORA.1 (DIR), ORA.20 (VCC), ORB.1 (DIR), ORB.20 (VCC), XOR1.14 (VCC), XOR2.14 (VCC), XOR3.14 (VCC), XOR4.14 (VCC), XORA.1 (DIR), XORA.20 (VCC), XORB.1 (DIR), XORB.20 (VCC); also elsewhere on the board
